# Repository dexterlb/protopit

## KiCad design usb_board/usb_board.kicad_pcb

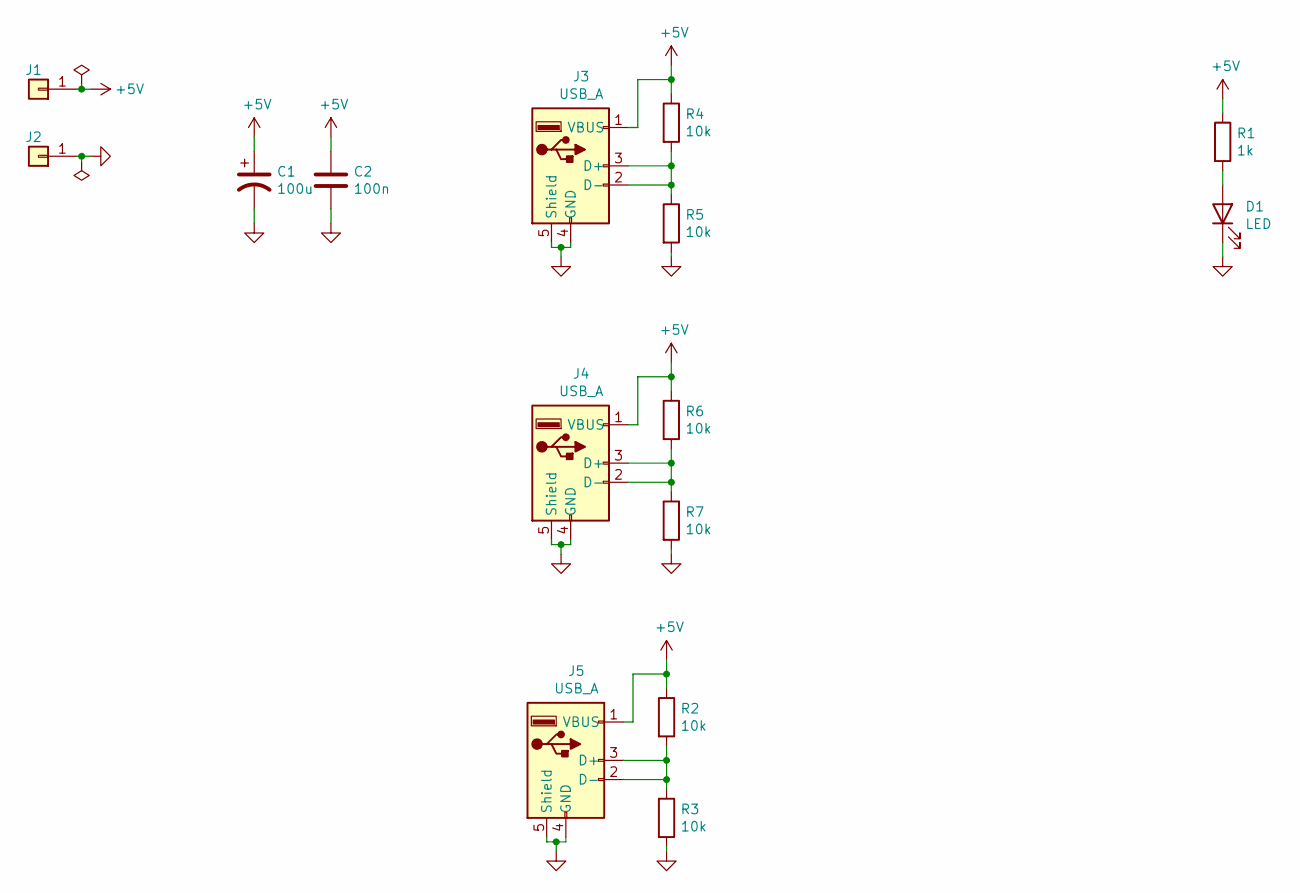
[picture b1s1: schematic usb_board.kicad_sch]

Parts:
C1: 100u; CP_Radial_D6.3mm_P2.50mm
C2: 100n; C_0805_2012Metric_Pad1.15x1.40mm_HandSolder
D1: LED; LED_D5.0mm
J1, J2: IN_5V; 1PIN_DG306
J3, J4, J5: USB_A; USB_A_CVILUX_VERTICAL
R1: 1k; R_0805_2012Metric_Pad1.15x1.40mm_HandSolder
R2, R3, R4, R5, R6, R7: 10k; R_0805_2012Metric_Pad1.15x1.40mm_HandSolder

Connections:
+5V: C1.1, C2.1, J1.1, J3.1 (VBUS), J4.1 (VBUS), J5.1 (VBUS), R1.1, R2.1, R4.1, R6.1
GND: C1.2, C2.2, D1.1 (K), J2.1, J3.4 (GND), J3.5 (Shield), J4.4 (GND), J4.5 (Shield), J5.4 (GND), J5.5 (Shield), R3.2, R5.2, R7.2
unnamed: D1.2 (A), R1.2
unnamed: J3.2 (D-), J3.3 (D+), R4.2, R5.1
unnamed: J4.2 (D-), J4.3 (D+), R6.2, R7.1
unnamed: J5.2 (D-), J5.3 (D+), R2.2, R3.1

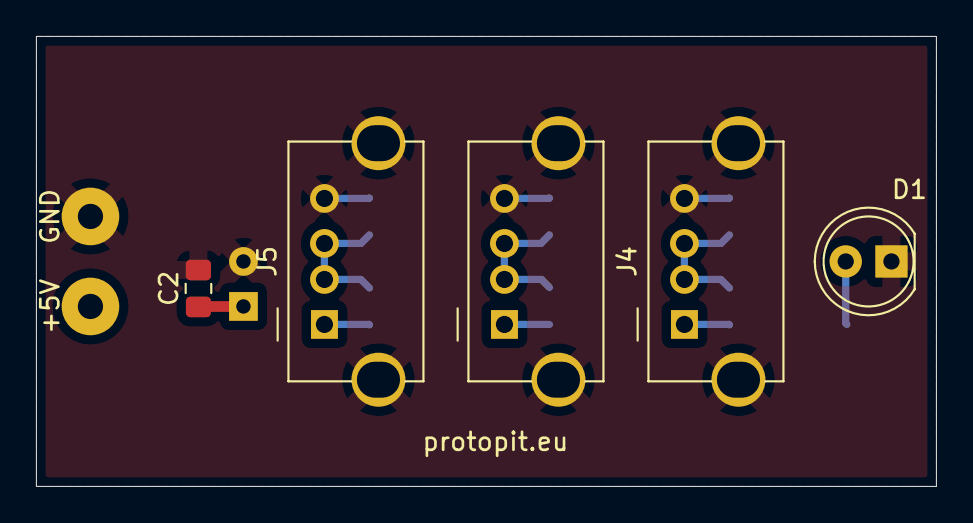
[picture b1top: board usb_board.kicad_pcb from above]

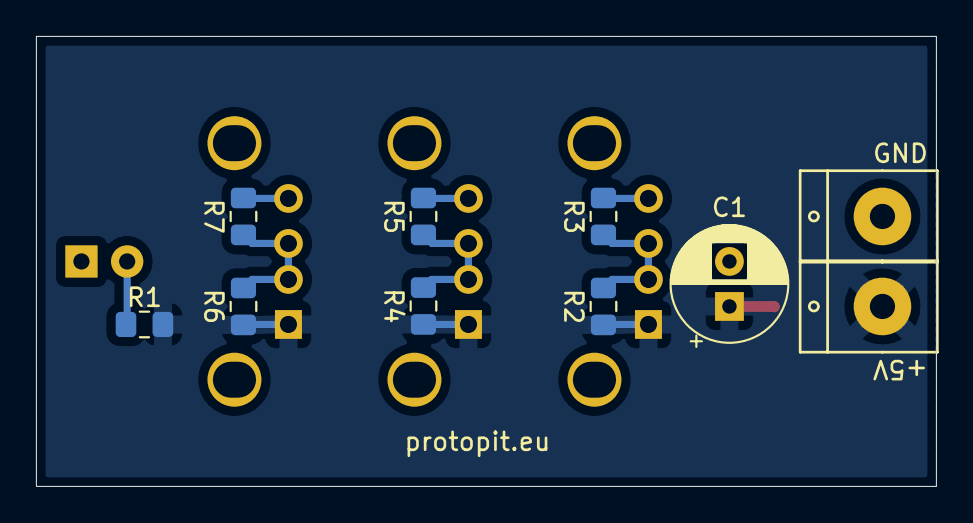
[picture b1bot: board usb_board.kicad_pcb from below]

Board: 2 copper layers, 50.0 x 25.0 mm, 15 parts (10 on the bottom side), 6 nets.

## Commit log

2019-04-09 basic scaffold for site
2019-04-09 add metadata
2019-04-09 implement CSS
2019-04-09 implement base64 image loading from css
2019-04-10 simple cli
2019-04-10 markdown extensions
2019-04-10 some fonts
2019-04-10 moar css
2019-04-10 html transformations
2019-04-10 urls to pages
2019-04-10 fix bug
2019-04-10 introduce list of pages by date
2019-04-11 landing page template and proper language handling
2019-04-11 fix page name handling
2019-04-11 default to normal pages
2019-04-11 translator
2019-04-11 more dummy files to test languages
2019-04-12 move cli to internal dir
2019-04-14 cache intermediate media results
2019-04-14 experimental support for images
2019-04-14 add squirrel image for testing
2019-04-15 image scaling works
2019-04-16 allow fancy hacks in templates
2019-04-17 page list
2019-04-17 tags and stuff
2019-04-18 almost finished event support
2019-04-20 events work
2019-04-20 cosmetic changes
2019-05-11 dummy translation
2019-05-24 dummy commit!
2019-05-24 remove all content
2019-05-24 Revert "remove all content"
    This reverts commit 4ba3c0b3e9529741c040a5af8930a2ba2cbbe2dc.
2019-05-24 show date for past events
2019-06-04 add logo
2019-06-04 make css files use the media api
2019-06-04 antialias svgs
2019-07-27 add feeds on pages
2019-08-01 prettier landing page
2019-08-01 better icons
2020-05-08 usb board
2020-06-04 update usb board
2022-12-20 Add stl->gcode protoprinter script
2022-12-21 Try 0.10 layer height
2024-10-01 update Prusa Slicer config to new version
2024-10-01 update gcode hacks
2024-10-01 home z
